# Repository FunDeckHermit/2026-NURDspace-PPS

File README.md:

## NURDspace PPS

This is a repo with the KiCAD hardware design for a USB PD PPS power supply. It is controlled by an ESP32-S3 running ESPHome exposing actions to Home Assistant. 

There is no numeric voltage indicator, LEDs are used in a ring around the rotary encoder to set the output PPS voltage.

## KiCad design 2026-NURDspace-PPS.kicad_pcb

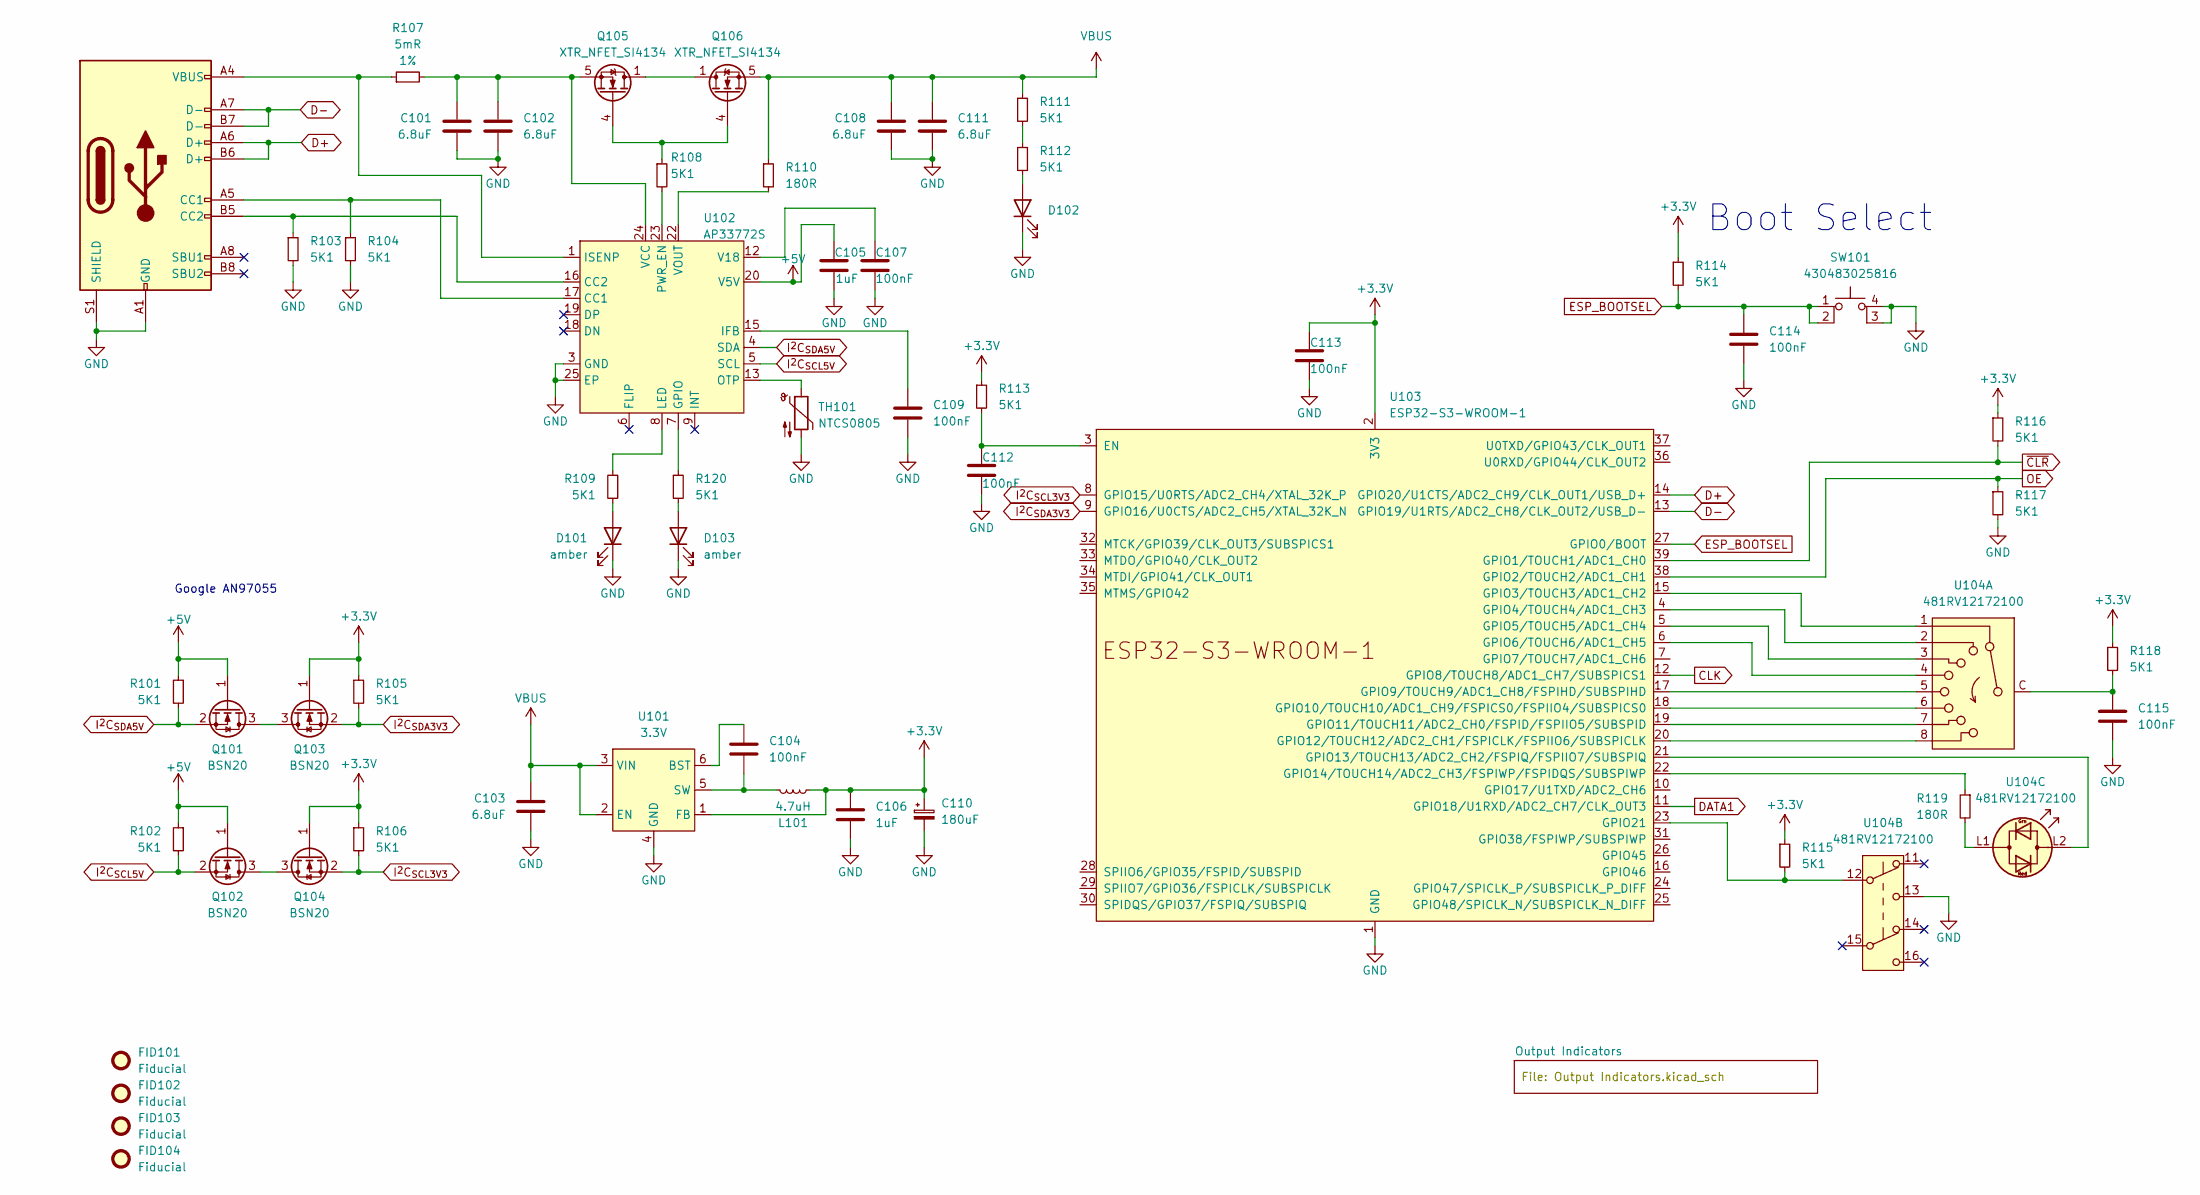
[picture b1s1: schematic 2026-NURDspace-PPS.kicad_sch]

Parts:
C101, C102, C103, C108, C111: 6.8uF; C_1206_3216Metric; Rated Voltage 50V; Tolerance ±10%; MPN 1206B685K500CT
C104, C107, C109, C112, C113, C114, C115: 100nF; C_0805_2012Metric; Rated Voltage 50V; Tolerance ±10%; MPN 0805B104K500CT
C105, C106: 1uF; C_1206_3216Metric; Rated Voltage 25V; Tolerance ±10%; MPN 1206B105K250CT
C110: 180uF; CP_Wurth_WCAP-PHLE-L7.3W4.3H1.9; MPN 875035119002
D101, D103: amber; LED_0603_1608Metric; MPN 150060AS75000
D102: brightgreen; LED_0603_1608Metric; MPN 150060VS75000
FID101, FID102, FID103, FID104: Fiducial; Fiducial_0.5mm_Mask1mm
J101: UJ20-C-H-C-4-SMT-TR; USB_C_Receptacle_SSKY_UJ20-C-H-C-4-SMT-TR; MPN UJ20-C-H-C-4-SMT-TR
L101: 4.7uH; L_1008_2520Metric_Pad1.43x2.20mm_HandSolder; MPN 74479889247
Q101, Q102, Q103, Q104: BSN20; SOT-23; MPN BSN20-7
Q105, Q106: XTR_NFET_SI4134; SOIC-8_3.9x4.9mm_P1.27mm; MPN SI4134DY-T1-E3
R101, R102, R103, R104, R105, R106, R108, R109, R111, R112, R113, R114, R115, R116, R117, R118, R120: 5K1; R_0805_2012Metric; MPN RC0805FR-075K1L
R107: 5mR; R_0805_2012Metric_Pad1.20x1.40mm_HandSolder; Tolerance 1%; MPN 580060720003
R110, R119: 180R; R_0805_2012Metric; MPN RC0805FR-07180RL
SW101: 430483025816; SW_Push_430483025816; MPN 430483025816
TH101: NTCS0805; R_0805_2012Metric; MPN NTCS0805E3103HHT
U101: 3.3V; TSOT-23-6; MPN AP63203WU-7
U102: AP33772S; QFN-24-1EP_4x4mm_P0.5mm_EP2.6x2.6mm; LCSC C9900152998
U103: ESP32-S3-WROOM-1; MPN ESP32-S3-WROOM-1-N8R8
U104: 481RV12172100; MPN 481RV12172100

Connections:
+3.3V: C106.1, C110.1, C113.1, L101.2, Q103.1 (G), Q104.1 (G), R105.1, R106.1, R113.1, R114.1, R115.1, R116.1, R118.1, U101.1 (FB), U103.2 (3V3); also elsewhere on the board
+5V: C105.1, Q101.1 (G), Q102.1 (G), R101.1, R102.1, U102.20 (V5V)
CLK: U103.12 (GPIO8/TOUCH8/ADC1_CH7/SUBSPICS1); also elsewhere on the board
D+: J101.A6 (D+), J101.B6 (D+), U103.14 (GPIO20/U1CTS/ADC2_CH9/CLK_OUT1/USB_D+)
D-: J101.A7 (D-), J101.B7 (D-), U103.13 (GPIO19/U1RTS/ADC2_CH8/CLK_OUT2/USB_D-)
DATA1: U103.11 (GPIO18/U1RXD/ADC2_CH7/CLK_OUT3); also elsewhere on the board
ESP_BOOTSEL: C114.1, R114.2, SW101.1, SW101.2, U103.27 (GPIO0/BOOT)
GND: C101.2, C102.2, C103.2, C105.2, C106.2, C107.2, C108.2, C109.2, C110.2, C111.2, C112.2, C113.2, C114.2, C115.2, D101.1 (K), D102.1 (K), D103.1 (K), J101.A1 (GND), J101.A12 (GND), J101.B1 (GND), J101.B12 (GND), J101.S1 (SHIELD), R103.2, R104.2, R117.2, SW101.3, SW101.4, TH101.2, U101.4 (GND), U102.3 (GND), U102.25 (EP), U103.1 (GND), U103.40 (GND), U103.41 (GND), U104.13; also elsewhere on the board
I^{2}C_{SCL3V3}: Q104.2 (S), R106.2, U103.8 (GPIO15/U0RTS/ADC2_CH4/XTAL_32K_P)
I^{2}C_{SCL5V}: Q102.2 (S), R102.2, U102.5 (SCL)
I^{2}C_{SDA3V3}: Q103.2 (S), R105.2, U103.9 (GPIO16/U0CTS/ADC2_CH5/XTAL_32K_N)
I^{2}C_{SDA5V}: Q101.2 (S), R101.2, U102.4 (SDA)
unnamed: C115.1, R118.2, U104.C
unnamed: D101.2 (A), R109.2
unnamed: D102.2 (A), R112.2
unnamed: D103.2 (A), R120.2
unnamed: J101.A5 (CC1), R104.1, U102.17 (CC1)
unnamed: J101.B5 (CC2), R103.1, U102.16 (CC2)
unnamed: Q101.3 (D), Q103.3 (D)
unnamed: Q102.3 (D), Q104.3 (D)
unnamed: Q105.4 (G), Q106.4 (G), R108.1
unnamed: Q105.1 (S), Q105.2 (S), Q105.3 (S), Q106.1 (S), Q106.2 (S), Q106.3 (S)
unnamed: R111.2, R112.1
unnamed: R119.2, U104.L1
unnamed: C104.1, U101.6 (BST)
unnamed: C104.2, L101.1, U101.5 (SW)
unnamed: R120.1, U102.7 (GPIO)
unnamed: C109.1, U102.15 (IFB)
unnamed: J101.A4 (VBUS), J101.A9 (VBUS), J101.B4 (VBUS), J101.B9 (VBUS), R107.1, U102.1 (ISENP)
unnamed: R109.1, U102.8 (LED)
unnamed: TH101.1, U102.13 (OTP)
unnamed: R108.2, U102.23 (PWR_EN)
unnamed: C107.1, U102.12 (V18)
unnamed: C101.1, C102.1, Q105.5 (D), Q105.6 (D), Q105.7 (D), Q105.8 (D), R107.2, U102.24 (VCC)
unnamed: R110.2, U102.22 (VOUT)
unnamed: C112.1, R113.2, U103.3 (EN)
unnamed: U103.15 (GPIO3/TOUCH3/ADC1_CH2), U104.1
unnamed: U103.4 (GPIO4/TOUCH4/ADC1_CH3), U104.2
unnamed: U103.5 (GPIO5/TOUCH5/ADC1_CH4), U104.3
unnamed: U103.6 (GPIO6/TOUCH6/ADC1_CH5), U104.4
unnamed: U103.17 (GPIO9/TOUCH9/ADC1_CH8/FSPIHD/SUBSPIHD), U104.5
unnamed: U103.18 (GPIO10/TOUCH10/ADC1_CH9/FSPICS0/FSPIIO4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), U104.6
unnamed: U103.19 (GPIO11/TOUCH11/ADC2_CH0/FSPID/FSPIIO5/S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), U104.7
unnamed: U103.20 (GPIO12/TOUCH12/ADC2_CH1/FSPICLK/FSPIIO6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), U104.8
unnamed: U103.21 (GPIO13/TOUCH13/ADC2_CH2/FSPIQ/FSPIIO7/S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), U104.L2
unnamed: R119.1, U103.22 (GPIO14/TOUCH14/ADC2_CH3/FSPIWP/FSPIDQS/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)
unnamed: R115.2, U103.23 (GPIO21), U104.12
OE: R117.1, U103.38 (GPIO2/TOUCH2/ADC1_CH1); also elsewhere on the board
VBUS: C103.1, C108.1, C111.1, Q106.5 (D), Q106.6 (D), Q106.7 (D), Q106.8 (D), R110.1, R111.1, U101.2 (EN), U101.3 (VIN); also elsewhere on the board
~CLR: R116.2, U103.39 (GPIO1/TOUCH1/ADC1_CH0); also elsewhere on the board

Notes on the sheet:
Boot Select
Google AN97055

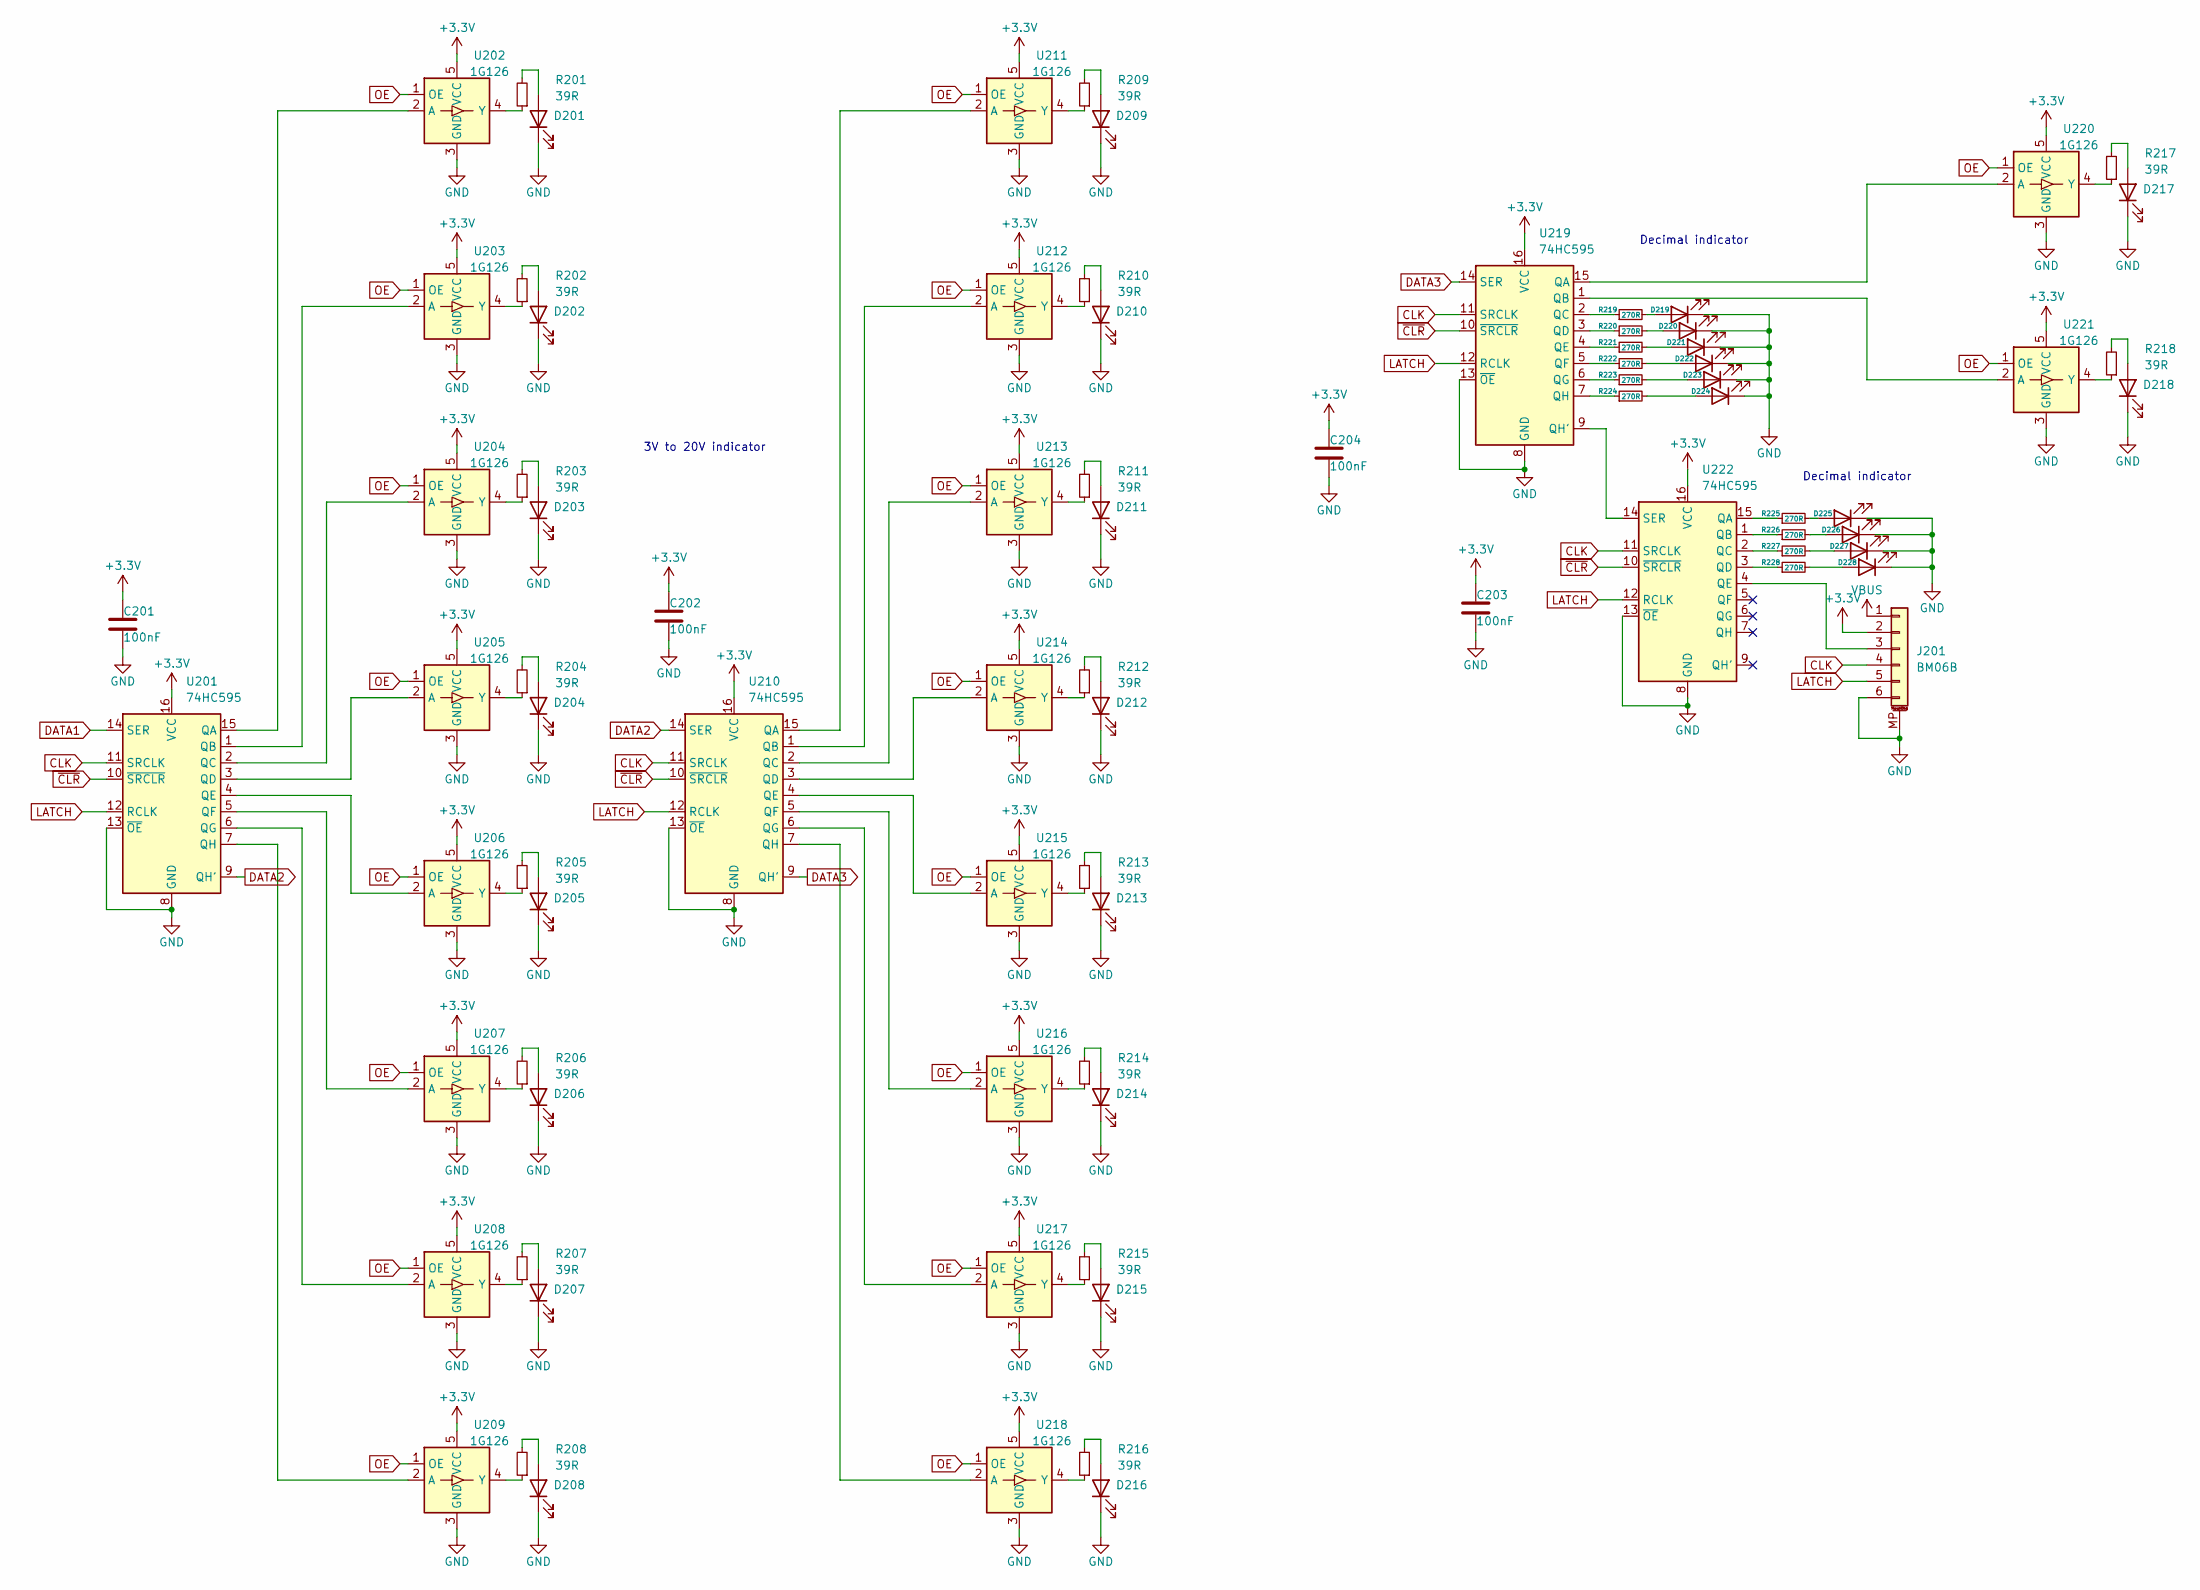
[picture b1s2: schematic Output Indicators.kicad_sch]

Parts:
C201, C202, C203, C204: 100nF; C_0805_2012Metric; Rated Voltage 50V; Tolerance ±10%; MPN 0805B104K500CT
D201, D202, D203, D204, D205, D206, D207, D208, D209, D210, D211, D212, D213, D214, D215, D216, D217, D218: MXA8-PW40-0000; LED_Luxeon3535_3.5x3.7mm; MPN MXA8-PW40-0000
D219, D220, D221, D222, D223, D224, D225, D226, D227, D228: Led_0603_superred_generic; LED_0603_1608Metric; MPN 150060SS75000
J201: BM06B; J_BM06B-GHS-TBT; MPN BM06B-GHS-TBT(LF)(SN)
R201, R202, R203, R204, R205, R206, R207, R208, R209, R210, R211, R212, R213, R214, R215, R216, R217, R218: 39R; R_0805_2012Metric; MPN RC0805FR-0739RL
R219, R220, R221, R222, R223, R224, R225, R226, R227, R228: 270R; R_0805_2012Metric; MPN RC0805FR-07270RL
U201, U210, U219, U222: 74HC595; SOIC-16_3.9x9.9mm_P1.27mm; MPN 74HC595D
U202, U203, U204, U205, U206, U207, U208, U209, U211, U212, U213, U214, U215, U216, U217, U218, U220, U221: 1G126; SOT-353_SC-70-5; MPN sn74lv1t126

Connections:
+3.3V: C201.1, C202.1, C203.1, C204.1, J201.2, U201.16 (VCC), U202.5 (VCC), U203.5 (VCC), U204.5 (VCC), U205.5 (VCC), U206.5 (VCC), U207.5 (VCC), U208.5 (VCC), U209.5 (VCC), U210.16 (VCC), U211.5 (VCC), U212.5 (VCC), U213.5 (VCC), U214.5 (VCC), U215.5 (VCC), U216.5 (VCC), U217.5 (VCC), U218.5 (VCC), U219.16 (VCC), U220.5 (VCC), U221.5 (VCC), U222.16 (VCC); also elsewhere on the board
CLK: J201.4, U201.11 (SRCLK), U210.11 (SRCLK), U219.11 (SRCLK), U222.11 (SRCLK); also elsewhere on the board
DATA1: U201.14 (SER); also elsewhere on the board
DATA2: U201.9 (QH'), U210.14 (SER)
DATA3: U210.9 (QH'), U219.14 (SER)
GND: C201.2, C202.2, C203.2, C204.2, D201.1 (K), D202.1 (K), D203.1 (K), D204.1 (K), D205.1 (K), D206.1 (K), D207.1 (K), D208.1 (K), D209.1 (K), D210.1 (K), D211.1 (K), D212.1 (K), D213.1 (K), D214.1 (K), D215.1 (K), D216.1 (K), D217.1 (K), D218.1 (K), D219.1 (K), D220.1 (K), D221.1 (K), D222.1 (K), D223.1 (K), D224.1 (K), D225.1 (K), D226.1 (K), D227.1 (K), D228.1 (K), J201.6, J201.MP (MountPin), U201.8 (GND), U201.13 (~OE), U202.3 (GND), U203.3 (GND), U204.3 (GND), U205.3 (GND), U206.3 (GND), U207.3 (GND), U208.3 (GND), U209.3 (GND), U210.8 (GND), U210.13 (~OE), U211.3 (GND), U212.3 (GND), U213.3 (GND), U214.3 (GND), U215.3 (GND), U216.3 (GND), U217.3 (GND), U218.3 (GND), U219.8 (GND), U219.13 (~OE), U220.3 (GND), U221.3 (GND), U222.8 (GND), U222.13 (~OE); also elsewhere on the board
LATCH: J201.5, U201.12 (RCLK), U210.12 (RCLK), U219.12 (RCLK), U222.12 (RCLK)
unnamed: D201.2 (A), R201.2
unnamed: D202.2 (A), R202.2
unnamed: D203.2 (A), R203.2
unnamed: D204.2 (A), R204.2
unnamed: D205.2 (A), R205.2
unnamed: D206.2 (A), R206.2
unnamed: D207.2 (A), R207.2
unnamed: D208.2 (A), R208.2
unnamed: D209.2 (A), R209.2
unnamed: D210.2 (A), R210.2
unnamed: D211.2 (A), R211.2
unnamed: D212.2 (A), R212.2
unnamed: D213.2 (A), R213.2
unnamed: D214.2 (A), R214.2
unnamed: D215.2 (A), R215.2
unnamed: D216.2 (A), R216.2
unnamed: D217.2 (A), R217.2
unnamed: D218.2 (A), R218.2
unnamed: D219.2 (A), R219.2
unnamed: D220.2 (A), R220.2
unnamed: D221.2 (A), R221.2
unnamed: D222.2 (A), R222.2
unnamed: D223.2 (A), R223.2
unnamed: D224.2 (A), R224.2
unnamed: D225.2 (A), R225.2
unnamed: D226.2 (A), R226.2
unnamed: D227.2 (A), R227.2
unnamed: D228.2 (A), R228.2
unnamed: J201.3, U222.4 (QE)
unnamed: U201.15 (QA), U202.2 (A)
unnamed: U201.1 (QB), U203.2 (A)
unnamed: U201.2 (QC), U204.2 (A)
unnamed: U201.3 (QD), U205.2 (A)
unnamed: U201.4 (QE), U206.2 (A)
unnamed: U201.5 (QF), U207.2 (A)
unnamed: U201.6 (QG), U208.2 (A)
unnamed: U201.7 (QH), U209.2 (A)
unnamed: R201.1, U202.4 (Y)
unnamed: R202.1, U203.4 (Y)
unnamed: R203.1, U204.4 (Y)
unnamed: R204.1, U205.4 (Y)
unnamed: R205.1, U206.4 (Y)
unnamed: R206.1, U207.4 (Y)
unnamed: R207.1, U208.4 (Y)
unnamed: R208.1, U209.4 (Y)
unnamed: U210.15 (QA), U211.2 (A)
unnamed: U210.1 (QB), U212.2 (A)
unnamed: U210.2 (QC), U213.2 (A)
unnamed: U210.3 (QD), U214.2 (A)
unnamed: U210.4 (QE), U215.2 (A)
unnamed: U210.5 (QF), U216.2 (A)
unnamed: U210.6 (QG), U217.2 (A)
unnamed: U210.7 (QH), U218.2 (A)
unnamed: R209.1, U211.4 (Y)
unnamed: R210.1, U212.4 (Y)
unnamed: R211.1, U213.4 (Y)
unnamed: R212.1, U214.4 (Y)
unnamed: R213.1, U215.4 (Y)
unnamed: R214.1, U216.4 (Y)
unnamed: R215.1, U217.4 (Y)
unnamed: R216.1, U218.4 (Y)
unnamed: U219.15 (QA), U220.2 (A)
unnamed: U219.1 (QB), U221.2 (A)
unnamed: R219.1, U219.2 (QC)
unnamed: R220.1, U219.3 (QD)
unnamed: R221.1, U219.4 (QE)
unnamed: R222.1, U219.5 (QF)
unnamed: R223.1, U219.6 (QG)
unnamed: U219.9 (QH'), U222.14 (SER)
unnamed: R224.1, U219.7 (QH)
unnamed: R217.1, U220.4 (Y)
unnamed: R218.1, U221.4 (Y)
unnamed: R225.1, U222.15 (QA)
unnamed: R226.1, U222.1 (QB)
unnamed: R227.1, U222.2 (QC)
unnamed: R228.1, U222.3 (QD)
OE: U202.1 (OE), U203.1 (OE), U204.1 (OE), U205.1 (OE), U206.1 (OE), U207.1 (OE), U208.1 (OE), U209.1 (OE), U211.1 (OE), U212.1 (OE), U213.1 (OE), U214.1 (OE), U215.1 (OE), U216.1 (OE), U217.1 (OE), U218.1 (OE), U220.1 (OE), U221.1 (OE); also elsewhere on the board
VBUS: J201.1; also elsewhere on the board
~CLR: U201.10 (~SRCLR), U210.10 (~SRCLR), U219.10 (~SRCLR), U222.10 (~SRCLR); also elsewhere on the board

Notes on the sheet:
Decimal indicator
3V to 20V indicator

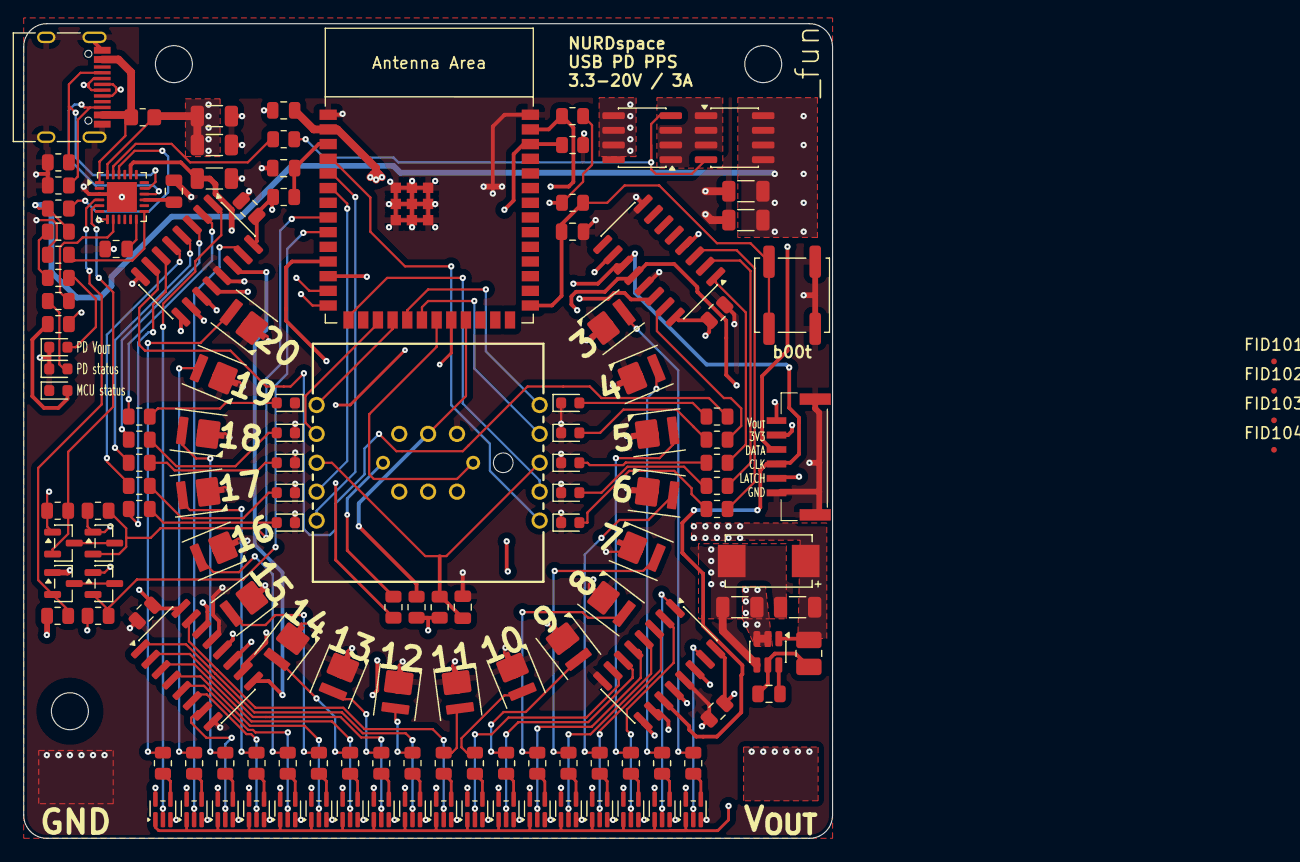
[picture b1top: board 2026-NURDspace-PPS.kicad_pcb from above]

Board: 4 copper layers, 70.0 x 70.5 mm, 139 parts (0 on the bottom side), 129 nets.

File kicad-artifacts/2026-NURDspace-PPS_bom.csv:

"Designator"," Comment"," MPN"," Footprint"," Quantity"
"C101,C102,C103,C108,C111","6.8uF","1206B685K500CT","Capacitor_SMD:C_1206_3216Metric","5"
"C104,C107,C109,C112,C113,C114,C115,C201,C202,C203,C204","100nF","0805B104K500CT","Capacitor_SMD:C_0805_2012Metric","11"
"C105,C106","1uF","1206B105K250CT","Capacitor_SMD:C_1206_3216Metric","2"
"C110","180uF","875035119002","0_NRD_footprints:CP_Wurth_WCAP-PHLE-L7.3W4.3H1.9","1"
"D101,D103","amber","150060AS75000","LED_SMD:LED_0603_1608Metric","2"
"D102","brightgreen","150060VS75000","LED_SMD:LED_0603_1608Metric","1"
"D201,D202,D203,D204,D205,D206,D207,D208,D209,D210,D211,D212,D213,D214,D215,D216,D217,D218","MXA8-PW40-0000","MXA8-PW40-0000","0_NRD_footprints:LED_Luxeon3535_3.5x3.7mm","18"
"D219,D220,D221,D222,D223,D224,D225,D226,D227,D228","Led_0603_superred_generic","150060SS75000","LED_SMD:LED_0603_1608Metric","10"
"J101","UJ20-C-H-C-4-SMT-TR","UJ20-C-H-C-4-SMT-TR","0_NRD_footprints:USB_C_Receptacle_SSKY_UJ20-C-H-C-4-SMT-TR","1"
"J201","BM06B","BM06B-GHS-TBT(LF)(SN) ","0_NRD_footprints:J_BM06B-GHS-TBT","1"
"L101","4.7uH","74479889247","Inductor_SMD:L_1008_2520Metric_Pad1.43x2.20mm_HandSolder","1"
"Q101,Q102,Q103,Q104","BSN20"," BSN20-7","Package_TO_SOT_SMD:SOT-23","4"
"Q105,Q106","XTR_NFET_SI4134","SI4134DY-T1-E3","Package_SO:SOIC-8_3.9x4.9mm_P1.27mm","2"
"R101,R102,R103,R104,R105,R106,R108,R109,R111,R112,R113,R114,R115,R116,R117,R118,R120","5K1","RC0805FR-075K1L","Resistor_SMD:R_0805_2012Metric","17"
"R107","5mR","580060720003","Resistor_SMD:R_0805_2012Metric_Pad1.20x1.40mm_HandSolder","1"
"R110,R119","180R","RC0805FR-07180RL","Resistor_SMD:R_0805_2012Metric","2"
"R201,R202,R203,R204,R205,R206,R207,R208,R209,R210,R211,R212,R213,R214,R215,R216,R217,R218","39R","RC0805FR-0739RL","Resistor_SMD:R_0805_2012Metric","18"
"R219,R220,R221,R222,R223,R224,R225,R226,R227,R228","270R","RC0805FR-07270RL","Resistor_SMD:R_0805_2012Metric","10"
"SW101","430483025816","430483025816","0_NRD_footprints:SW_Push_430483025816","1"
"TH101","NTCS0805","NTCS0805E3103HHT","Resistor_SMD:R_0805_2012Metric","1"
"U101","3.3V"," AP63203WU-7","Package_TO_SOT_SMD:TSOT-23-6","1"
"U102","AP33772S","","Interface_USBC:QFN-24-1EP_4x4mm_P0.5mm_EP2.6x2.6mm","1"
"U103","ESP32-S3-WROOM-1","ESP32-S3-WROOM-1-N8R8","0_NRD_footprints:ESP32-S3-WROOM-1","1"
"U104","481RV12172100","481RV12172100","0_NRD_footprints:481RV12172100","1"
"U201,U210,U219,U222","74HC595","74HC595D","Package_SO:SOIC-16_3.9x9.9mm_P1.27mm","4"
"U202,U203,U204,U205,U206,U207,U208,U209,U211,U212,U213,U214,U215,U216,U217,U218,U220,U221","1G126","sn74lv1t126","Package_TO_SOT_SMD:SOT-353_SC-70-5","18"

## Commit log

2026-02-28 Added NURDspace template
2026-02-28 Started on gathering parts
2026-03-02 Added all components
2026-03-02 Regenerated all outputs
2026-03-02 Wrote a small readme
2026-04-05 Drawn the schematic
2026-04-06 First version of layout
2026-04-13 Added new version of artifact generator
2026-04-13 Added new better version of artifact generator
